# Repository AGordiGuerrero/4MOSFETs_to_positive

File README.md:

# 4MOSFETs_to_positive
Four N-channel MOSFETs switches with NPN drivers

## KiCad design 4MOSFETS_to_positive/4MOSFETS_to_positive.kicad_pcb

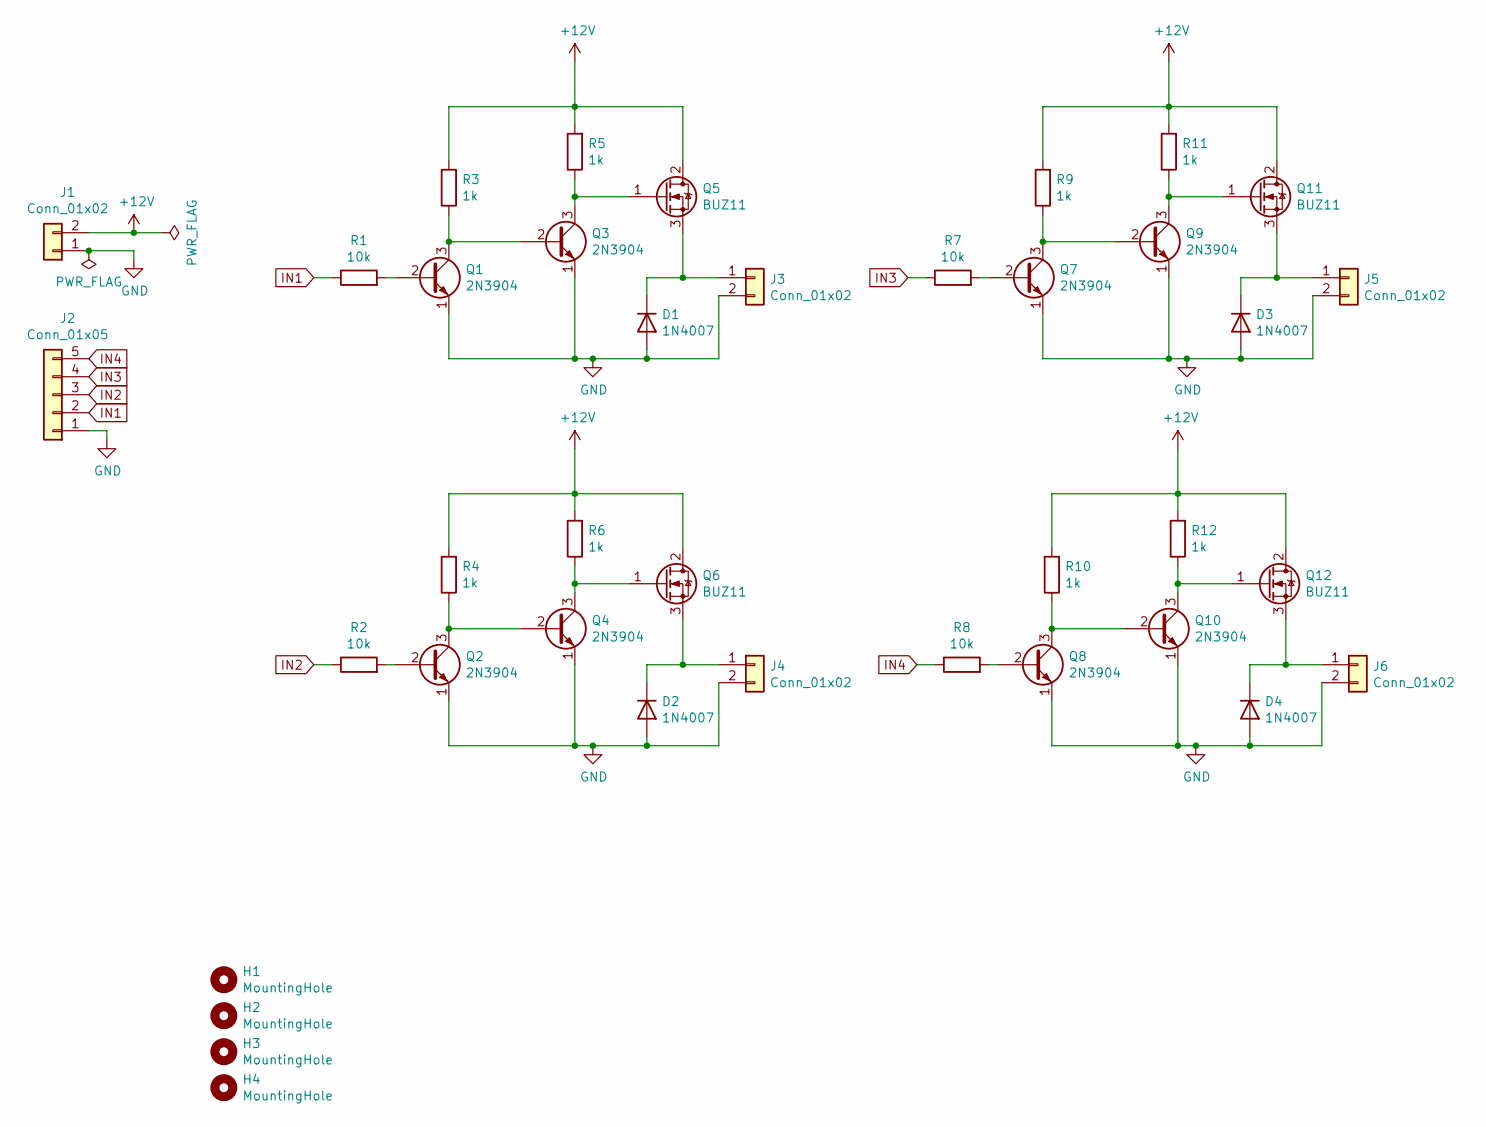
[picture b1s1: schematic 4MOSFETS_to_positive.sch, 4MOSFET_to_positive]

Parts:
D1, D2, D3, D4: 1N4007; D_DO-41_SOD81_P10.16mm_Horizontal
H1, H2, H3, H4: MountingHole; MountingHole_2.5mm
J1, J3, J4, J5, J6: Conn_01x02; TerminalBlock_Altech_AK300-2_P5.00mm
J2: Conn_01x05; PinHeader_1x05_P2.54mm_Vertical
Q1, Q2, Q3, Q4, Q7, Q8, Q9, Q10: 2N3904; TO-92_Inline
Q5, Q6, Q11, Q12: BUZ11; TO-220-3_Horizontal_TabDown
R1, R2, R7, R8: 10k; R_Axial_DIN0207_L6.3mm_D2.5mm_P7.62mm_Horizontal
R3, R4, R5, R6, R9, R10, R11, R12: 1k; R_Axial_DIN0207_L6.3mm_D2.5mm_P7.62mm_Horizontal

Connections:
+12V: J1.2, Q5.2 (D), Q6.2 (D), Q11.2 (D), Q12.2 (D), R3.2, R4.2, R5.2, R6.2, R9.2, R10.2, R11.2, R12.2
GND: D1.2 (A), D2.2 (A), D3.2 (A), D4.2 (A), J1.1, J2.1, J3.2, J4.2, J5.2, J6.2, Q1.1 (E), Q2.1 (E), Q3.1 (E), Q4.1 (E), Q7.1 (E), Q8.1 (E), Q9.1 (E), Q10.1 (E)
IN1: J2.2, R1.1
IN2: J2.3, R2.1
IN3: J2.4, R7.1
IN4: J2.5, R8.1
unnamed: D1.1 (K), J3.1, Q5.3 (S)
unnamed: D2.1 (K), J4.1, Q6.3 (S)
unnamed: D3.1 (K), J5.1, Q11.3 (S)
unnamed: D4.1 (K), J6.1, Q12.3 (S)
unnamed: Q1.2 (B), R1.2
unnamed: Q1.3 (C), Q3.2 (B), R3.1
unnamed: Q2.2 (B), R2.2
unnamed: Q2.3 (C), Q4.2 (B), R4.1
unnamed: Q3.3 (C), Q5.1 (G), R5.1
unnamed: Q4.3 (C), Q6.1 (G), R6.1
unnamed: Q7.2 (B), R7.2
unnamed: Q7.3 (C), Q9.2 (B), R9.1
unnamed: Q8.2 (B), R8.2
unnamed: Q8.3 (C), Q10.2 (B), R10.1
unnamed: Q10.3 (C), Q12.1 (G), R12.1
unnamed: Q9.3 (C), Q11.1 (G), R11.1

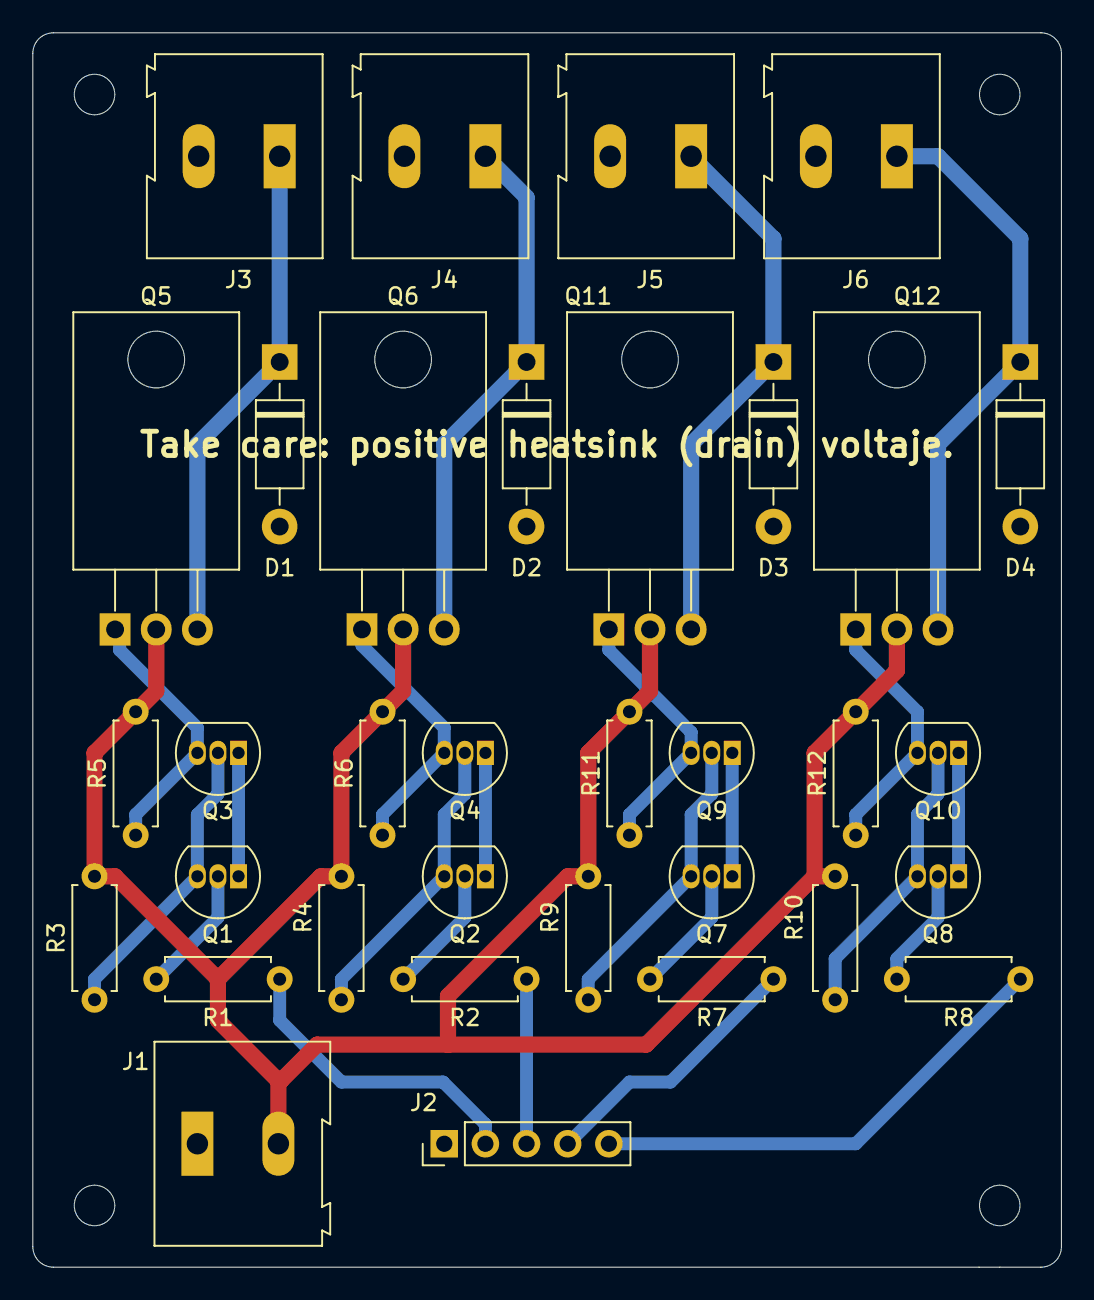
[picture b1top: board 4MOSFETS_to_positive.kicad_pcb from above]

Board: 2 copper layers, 63.5 x 76.2 mm, 38 parts (0 on the bottom side), 22 nets.
